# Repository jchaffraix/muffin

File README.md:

# muffin

A small mechanical keyboard for learning (and fun).

The goal is to build a small factor to learn how to build the PCB, soldering small components
and writing the firmware.

## Features

* USB-C connector.
* 5 keys, using Cherry MX or Kailh choc switches, including a 2U with a stabilizer.
* 1 rotary encoder.
* ATmega16 based.
* Mostly 805 SMT components.
* Include a programmer connector for ease of prototyping.
* A Muffin logo (because why not!?).

## PCB

The project relies on the [Keebio parts](https://github.com/keebio/Keebio-Parts.pretty) repository for the encoder and switch footprints.

To fetch the dependencies, run:

```
git submodule fetch
```

## Bill Of Materials

| Item | Package | Qty | Reference |
|------|---------|-----|-----------|
| 10uF Capacitor | SMT 805 | 1 | |
| 1uF Capacitor | SMT 805 | 1 | |
| .1uF Capacitor | SMT 805 | 4 | |
| 22pF Capacitor | SMT 805 | 2 | |
| Diode | SMT 805 | 5 | Rated 5V |
| 5.5V Zener Diode | SMT 805 | 1 |  |
| LED Red | SMT 805 | 1 | |
| LED Blue | SMT 805 | 1 | |
| LED Green | SMT 805 | 1 | |
| 10k resistor | SMT 805 | 1 | |
| 5.1k resistor | SMT 805 | 2 | |
| 330 resistor | SMT 805 | 4 | |
| 22 resistor | SMT 805 | 2 | |
| USB ESD protection | SOT-143 | 1 |  Used D1213A-02SR-7|
| USB C receptable (female) | | 1 | Used HRO-TYPE-C-31-M-12 |
| AVR-ISP-6 connector | | 1 | |
| RotaryEncoder Switch | | 1 | Used Alps EC11 |
| Cherry or Kailh choc Switches | | 5 | |
| Switch stabilizer for 2U | | 1 | |
| ATmega16U4-M | QFN-44 | 1 | ATmega32U4 should work too|
| 16MHz crystal | | 1 | Used 3155-16M20P2/49US-ND |
| Reset switch | | 1 | Used MJTP1117 |
| Optional programming Switch | SMT 254 | 1 | Used 2223-DS04-254-2-01BK-SMT-ND |

Note: The crystal and the 2pF capacitors can be omitted if you use the internal clock (which requires programming some bits on the ATmega16).

## Compiling and flashing

Coming soon.

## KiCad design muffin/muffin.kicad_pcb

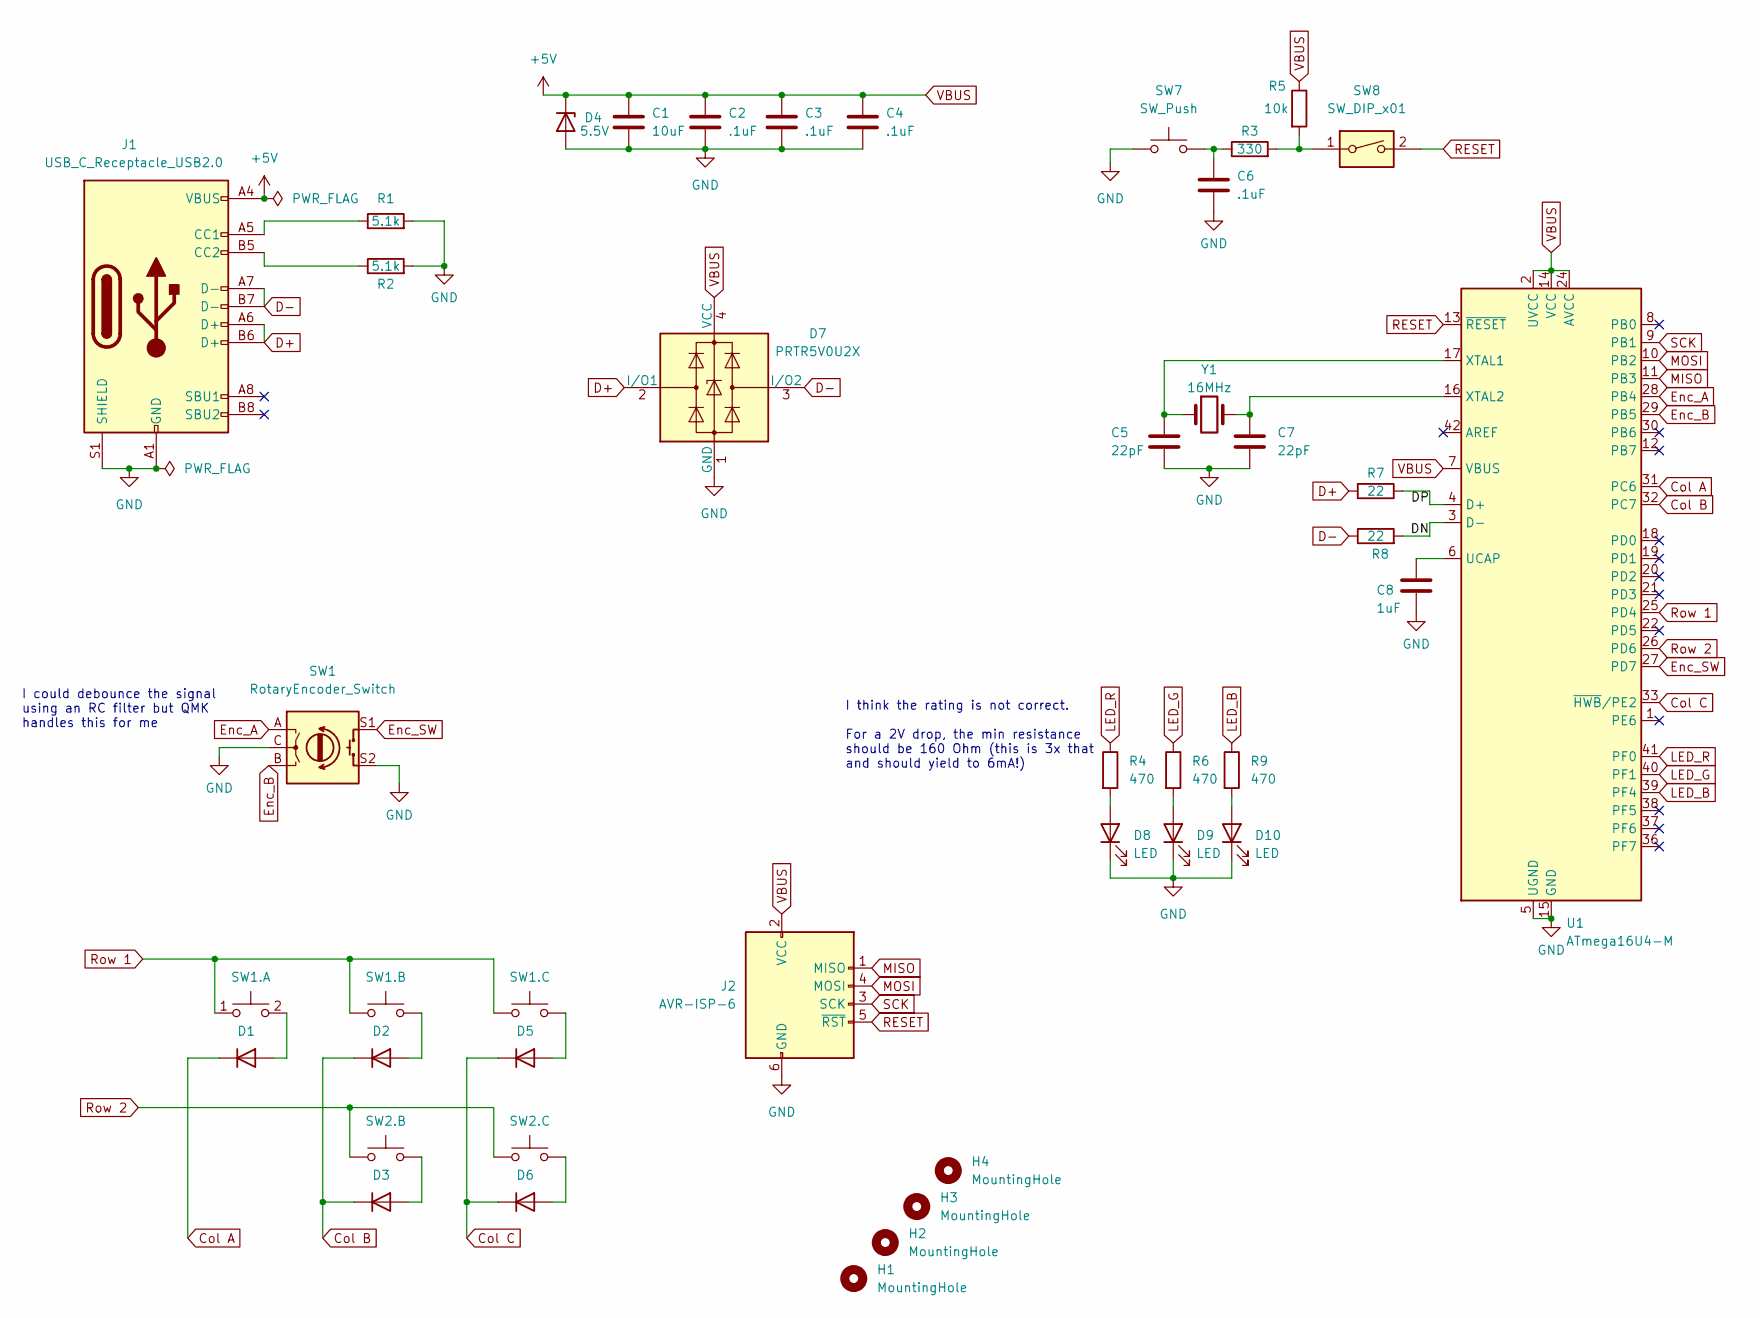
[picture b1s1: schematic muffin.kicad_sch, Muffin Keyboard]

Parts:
C1: 10uF; C_0805_2012Metric_Pad1.18x1.45mm_HandSolder
C2, C3, C4, C6: .1uF; C_0805_2012Metric_Pad1.18x1.45mm_HandSolder
C5, C7: 22pF; C_0805_2012Metric_Pad1.18x1.45mm_HandSolder
C8: 1uF; C_0805_2012Metric_Pad1.18x1.45mm_HandSolder
D1, D2, D3, D5, D6: D; D_0805_2012Metric_Pad1.15x1.40mm_HandSolder
D4: 5.5V; D_0805_2012Metric_Pad1.15x1.40mm_HandSolder
D7: PRTR5V0U2X; SOT-143
D8, D9, D10: LED; D_0805_2012Metric_Pad1.15x1.40mm_HandSolder
H1, H2, H3, H4: MountingHole; MountingHole_3.2mm_M3
J1: USB_C_Receptacle_USB2.0; HRO-TYPE-C-31-M-12-Assembly
J2: AVR-ISP-6; IDC-Header_2x03_P2.54mm_Horizontal
R1, R2: 5.1k; R_0805_2012Metric_Pad1.20x1.40mm_HandSolder
R3: 330; R_0805_2012Metric_Pad1.20x1.40mm_HandSolder
R4, R6, R9: 470; R_0805_2012Metric_Pad1.20x1.40mm_HandSolder
R5: 10k; R_0805_2012Metric_Pad1.20x1.40mm_HandSolder
R7, R8: 22; R_0805_2012Metric_Pad1.20x1.40mm_HandSolder
SW1: RotaryEncoder_Switch; RotaryEncoder_EC11
SW2: SW1.A; MX-Alps-Choc-2U
SW3: SW1.B; MX-Alps-Choc-1U-NoLED
SW4: SW2.B; MX-Alps-Choc-1U-NoLED
SW5: SW1.C; MX-Alps-Choc-1U-NoLED
SW6: SW2.C; MX-Alps-Choc-1U-NoLED
SW7: SW_Push; SW_Tactile_SPST_Angled_MJTP1117
SW8: SW_DIP_x01; DS04-254-SMT
U1: ATmega16U4-M; QFN-44-1EP_7x7mm_P0.5mm_EP5.2x5.2mm
Y1: 16MHz; Crystal_HC49-U_Vertical

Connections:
/DN: R8.2, U1.3 (D-)
/DP: R7.1, U1.4 (D+)
Col A: D1.1 (K), U1.31 (PC6)
Col B: D2.1 (K), D3.1 (K), U1.32 (PC7)
Col C: D5.1 (K), D6.1 (K), U1.33 (~HWB/PE2)
D+: D7.2 (I/O1), J1.A6 (D+), J1.B6 (D+), R7.2
D-: D7.3 (I/O2), J1.A7 (D-), J1.B7 (D-), R8.1
Enc_A: SW1.A, U1.28 (PB4)
Enc_B: SW1.B, U1.29 (PB5)
Enc_SW: SW1.S1, U1.27 (PD7)
GND: C1.2, C2.2, C3.2, C4.2, C5.2, C6.2, C7.2, C8.2, D4.2 (A), D7.1 (GND), D8.1 (K), D9.1 (K), D10.1 (K), J1.A1 (GND), J1.A12 (GND), J1.B1 (GND), J1.B12 (GND), J1.S1 (SHIELD), J2.6 (GND), R1.2, R2.2, SW1.C, SW1.S2, SW7.1, U1.5 (UGND), U1.15 (GND), U1.23 (GND), U1.35 (GND), U1.43 (GND), U1.45 (GND)
LED_B: R9.1, U1.39 (PF4)
LED_G: R6.1, U1.40 (PF1)
LED_R: R4.1, U1.41 (PF0)
MISO: J2.1 (MISO), U1.11 (PB3)
MOSI: J2.4 (MOSI), U1.10 (PB2)
unnamed: C5.1, U1.17 (XTAL1), Y1.1
unnamed: C6.1, R3.1, SW7.2
unnamed: C7.1, U1.16 (XTAL2), Y1.2
unnamed: C8.1, U1.6 (UCAP)
unnamed: D1.2 (A), SW2.2
unnamed: D2.2 (A), SW3.1
unnamed: D3.2 (A), SW4.1
unnamed: D5.2 (A), SW5.1
unnamed: D6.2 (A), SW6.1
unnamed: D8.2 (A), R4.2
unnamed: D9.2 (A), R6.2
unnamed: D10.2 (A), R9.2
unnamed: J1.A5 (CC1), R1.1
unnamed: J1.B5 (CC2), R2.1
unnamed: R3.2, R5.2, SW8.1
RESET: J2.5 (~RST), SW8.2, U1.13 (~RESET)
Row 1: SW2.1, SW3.2, SW5.2, U1.25 (PD4)
Row 2: SW4.2, SW6.2, U1.26 (PD6)
SCK: J2.3 (SCK), U1.9 (PB1)
VBUS: C1.1, C2.1, C3.1, C4.1, D4.1 (K), D7.4 (VCC), J1.A4 (VBUS), J1.A9 (VBUS), J1.B4 (VBUS), J1.B9 (VBUS), J2.2 (VCC), R5.1, U1.2 (UVCC), U1.7 (VBUS), U1.14 (VCC), U1.24 (AVCC), U1.34 (VCC), U1.44 (AVCC)

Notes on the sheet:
I could debounce the signal using an RC filter but QMK handles this for me
I think the rating is not correct. For a 2V drop, the min resistance should be 160 Ohm (this is 3x that and should yield to 6mA!)

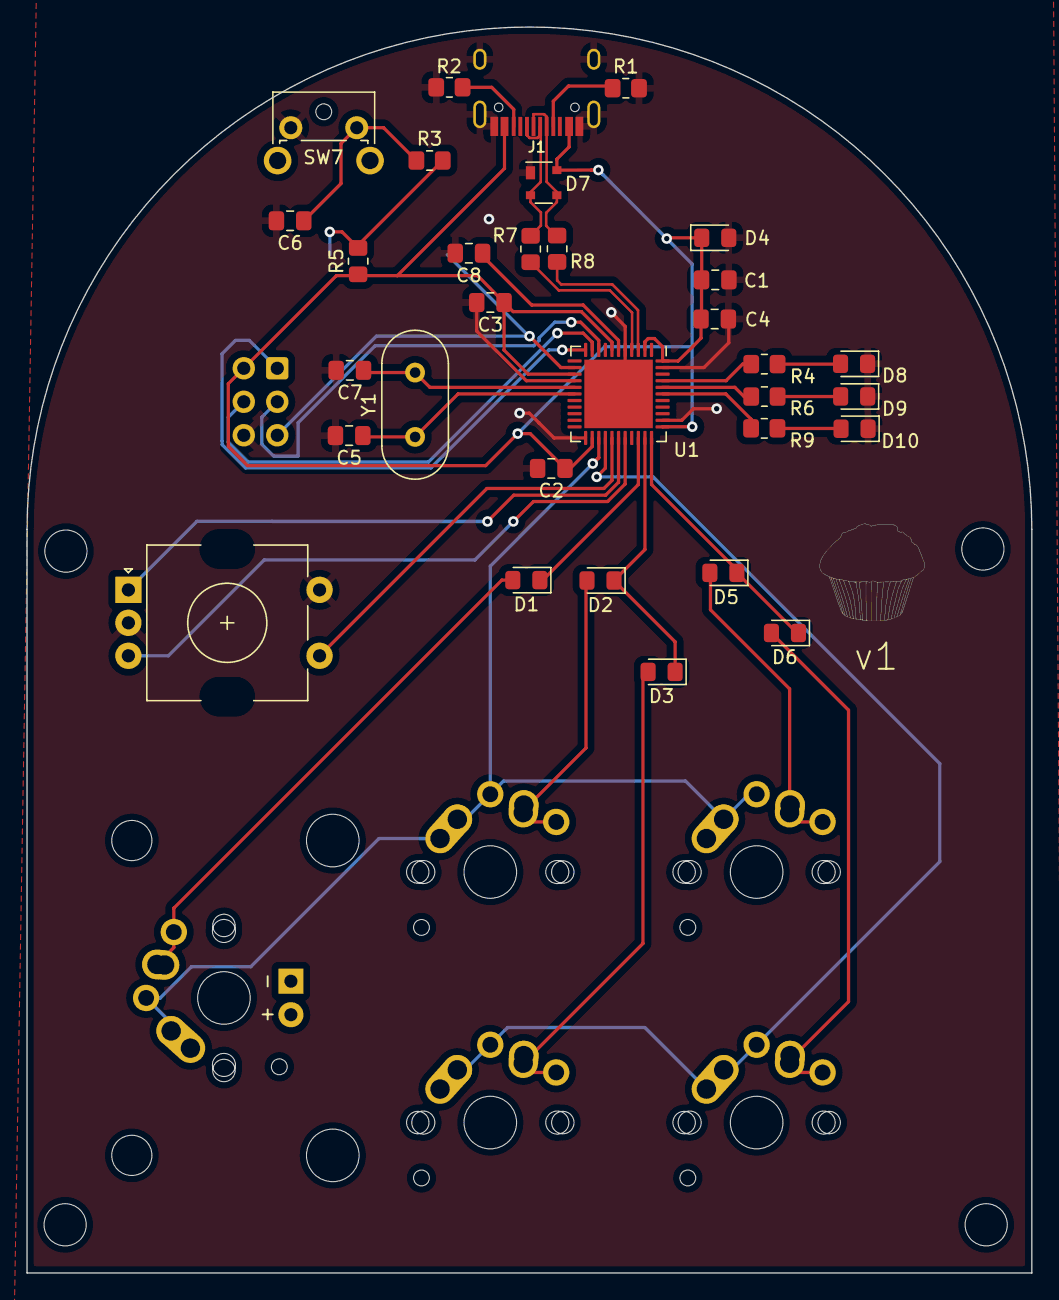
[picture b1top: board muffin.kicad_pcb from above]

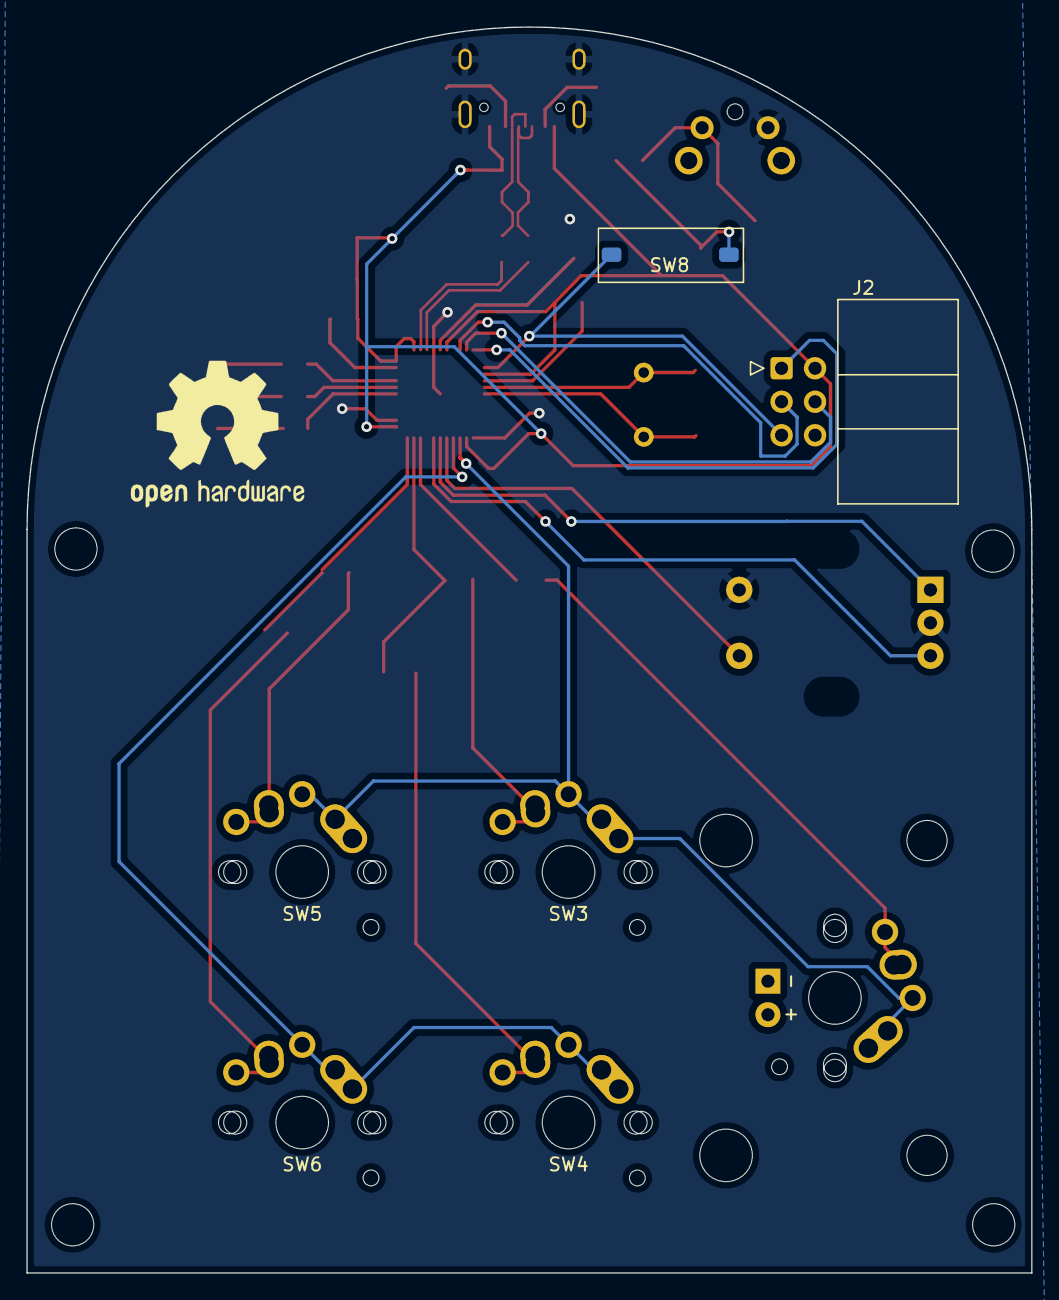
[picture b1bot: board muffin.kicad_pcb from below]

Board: 2 copper layers, 76.2 x 94.5 mm, 43 parts (2 on the bottom side), 36 nets.

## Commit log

2022-05-21 Fill the README
    Also corrected the resistor for the LEDs to simplify the BOM.
    The programming section will be filled when I get the PCB
    and solder the components.
2022-05-21 Add plans for v1
    The schematics is done and the PCB should
    be functional.
    I may decide to rework the diode layout.
2022-05-21 Update switches footprint
    I was using the LED version of the footprint for all 1U switches.
    I didn't change the 2U footprint as that would have required
    updating the Keebio library.
2022-05-22 Add the generated gerber files
    This allows checking the final output for the
    V1.
    While I included the schematics for the V1 that
    was used to generate the PCB.
